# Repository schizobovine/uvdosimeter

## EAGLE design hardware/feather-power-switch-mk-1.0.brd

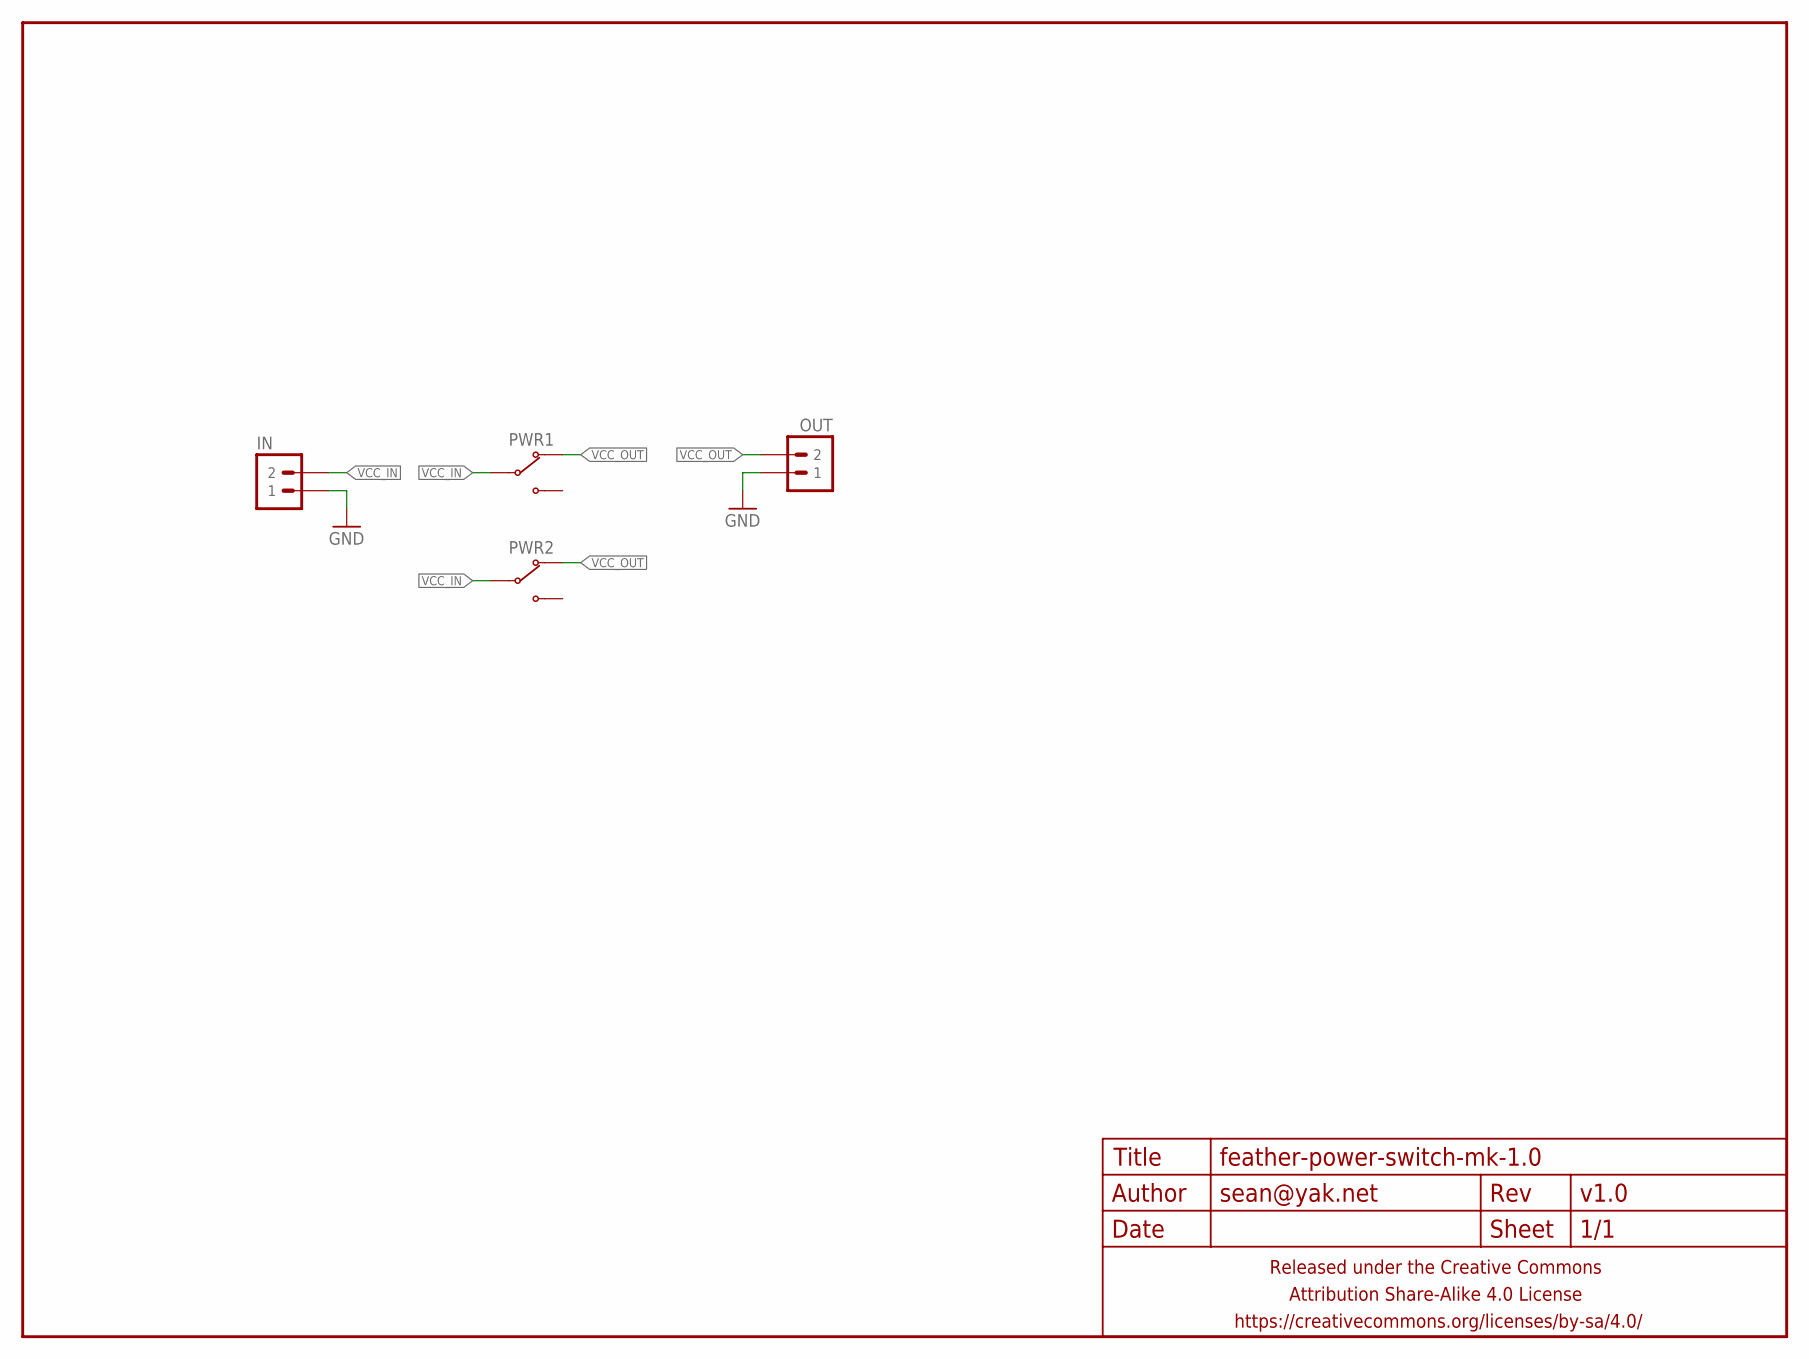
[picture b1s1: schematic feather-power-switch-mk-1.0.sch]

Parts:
FRAME1: FRAME-LETTERNO_PACKAGE; DUMMY
IN: M02JST-PTH-RA-R+; JST-2-PH-RA-PTH-R+
OUT: M02PTH-CENTERED-R+; 1X02-CENTER-R+
PWR1, PWR2: SWITCH-SPDTPCM12SMTR; SWITCH-SPDT-SMD-RA-PCM12SMTR

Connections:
GND: IN.1, OUT.1
VCC_IN: IN.2, PWR1.2 (COM), PWR2.2 (COM)
VCC_OUT: OUT.2, PWR1.1 (NC), PWR2.1 (NC)

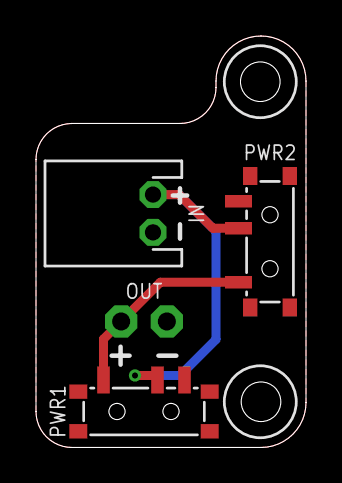
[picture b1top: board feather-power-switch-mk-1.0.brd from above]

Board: 2 copper layers, 15.0 x 22.9 mm, 5 parts (1 on the bottom side), 3 nets.

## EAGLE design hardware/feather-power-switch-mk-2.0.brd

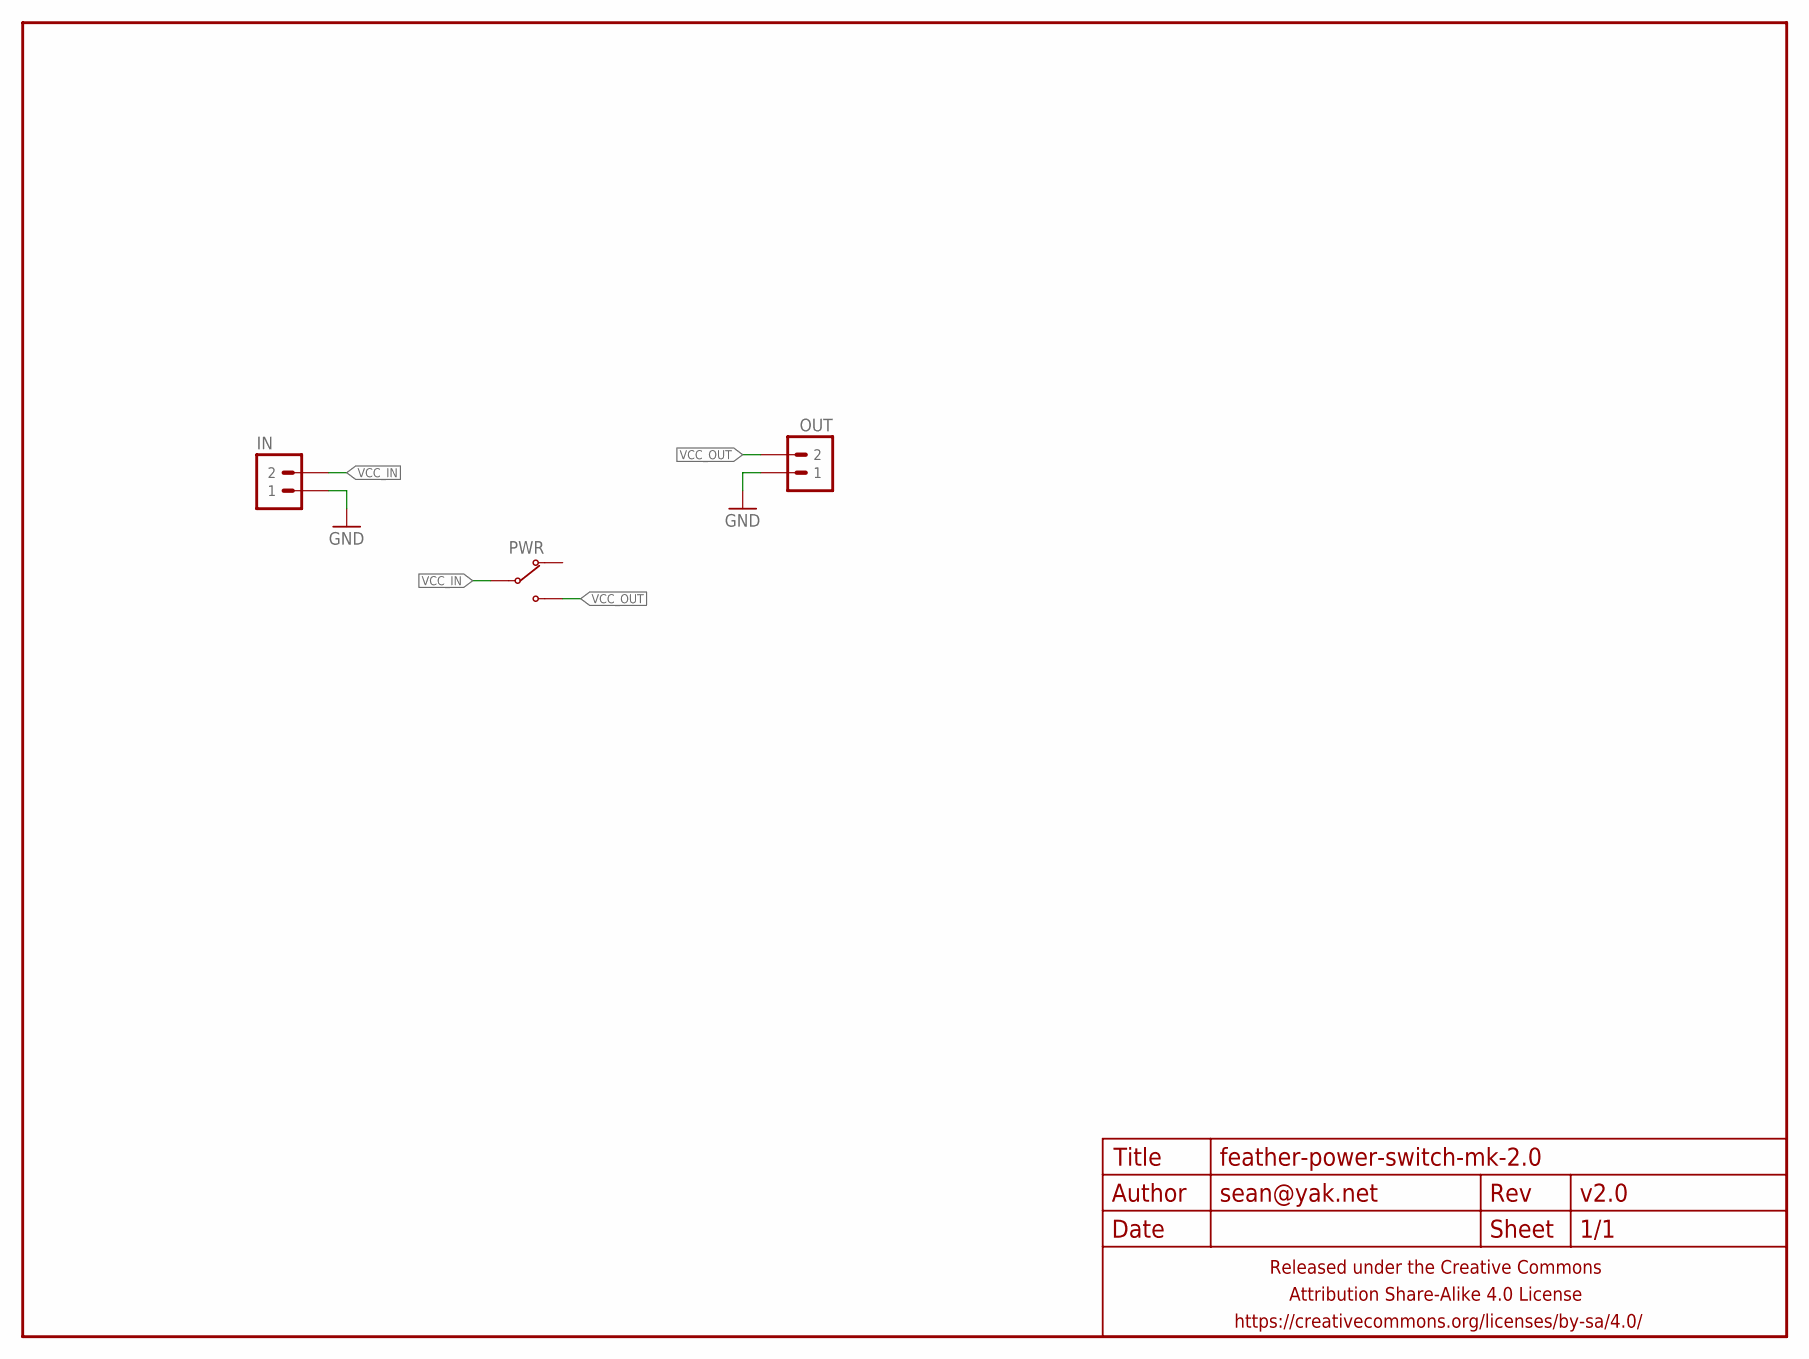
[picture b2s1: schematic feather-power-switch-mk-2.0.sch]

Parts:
FRAME1: FRAME-LETTERNO_PACKAGE; DUMMY
IN: M02PTH-CENTERED-R+; 1X02-CENTER-R+
OUT: M02PTH-CENTERED-R+; 1X02-CENTER-R+
PWR: SWITCH-SPDTSMD-RA; SWITCH-SPDT-SMD-RA

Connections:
GND: IN.1, OUT.1
VCC_IN: IN.2, PWR.2 (COM)
VCC_OUT: OUT.2, PWR.1 (NO)

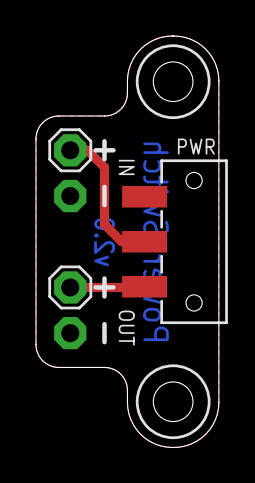
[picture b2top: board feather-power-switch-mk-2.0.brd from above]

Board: 2 copper layers, 10.2 x 22.9 mm, 4 parts (0 on the bottom side), 3 nets.

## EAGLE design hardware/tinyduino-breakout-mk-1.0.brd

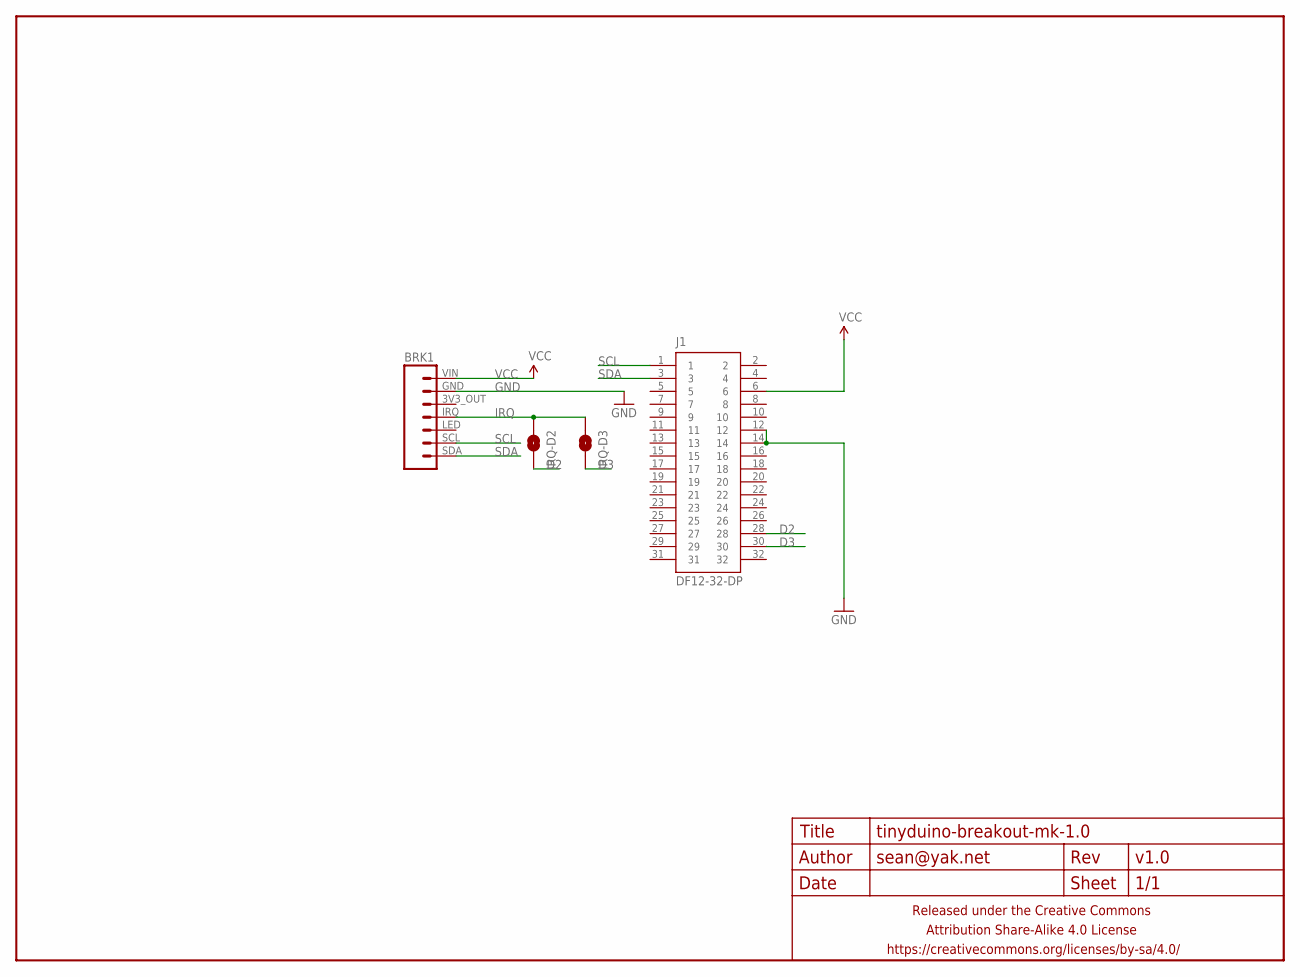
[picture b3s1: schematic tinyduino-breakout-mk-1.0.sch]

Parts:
BRK1: ADAFRUIT-SI1145-BREAKOUT
FRAME1: FRAME-LETTERNO_PACKAGE; DUMMY
IRQ-D2, IRQ-D3: JUMPER-PAD-2-NOYES_SILK; PAD-JUMPER-2-NO_YES_SILK
J1: DF12-32-DP

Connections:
D2: IRQ-D2.2, J1.28
D3: IRQ-D3.2, J1.30
GND: BRK1.GND, J1.12, J1.14
IRQ: BRK1.IRQ, IRQ-D2.1, IRQ-D3.1
SCL: BRK1.SCL, J1.1
SDA: BRK1.SDA, J1.3
VCC: BRK1.VIN, J1.6

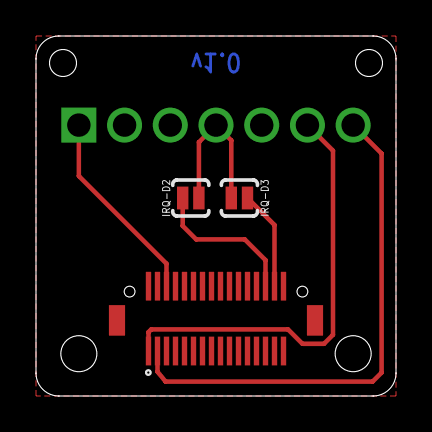
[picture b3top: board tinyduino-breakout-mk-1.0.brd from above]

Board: 2 copper layers, 20.0 x 20.0 mm, 5 parts (1 on the bottom side), 7 nets.

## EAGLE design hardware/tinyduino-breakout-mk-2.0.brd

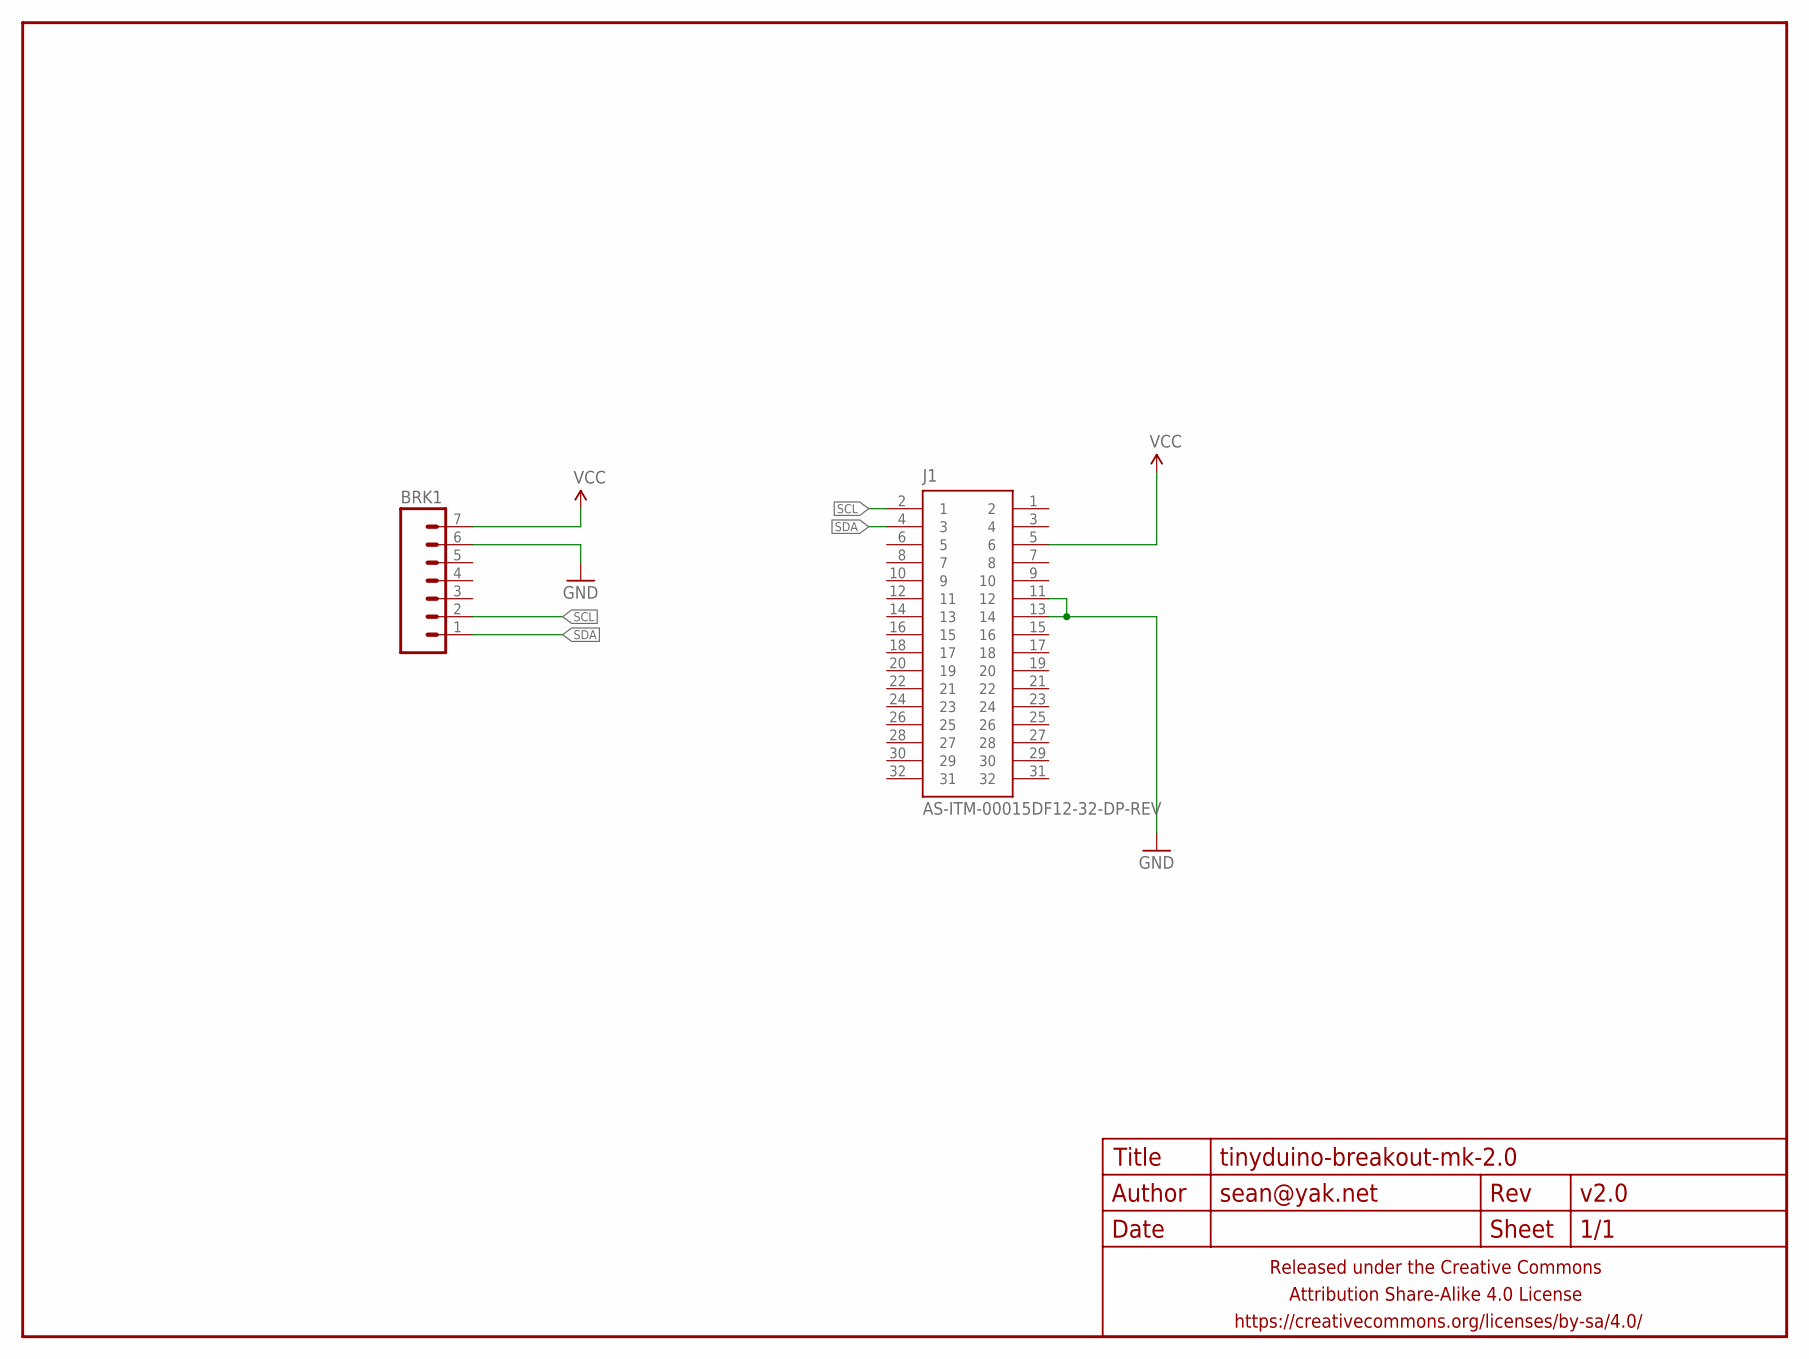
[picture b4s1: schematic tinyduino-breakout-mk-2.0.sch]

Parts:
BRK1: ADAFRUIT-SI1145-BREAKOUTSMD-RA; 1X07-SMD-SHORT
FRAME1: FRAME-LETTERNO_PACKAGE; DUMMY
J1: AS-ITM-00015DF12-32-DP-REV; DF12-32-DP

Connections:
GND: BRK1.6 (GND), J1.11 (12), J1.13 (14)
SCL: BRK1.2 (SCL), J1.2 (1)
SDA: BRK1.1 (SDA), J1.4 (3)
VCC: BRK1.7 (VIN), J1.5 (6)

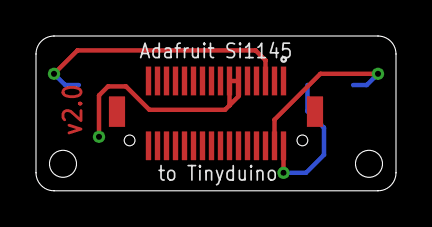
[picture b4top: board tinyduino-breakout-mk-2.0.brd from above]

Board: 2 copper layers, 20.0 x 8.6 mm, 3 parts (1 on the bottom side), 4 nets.

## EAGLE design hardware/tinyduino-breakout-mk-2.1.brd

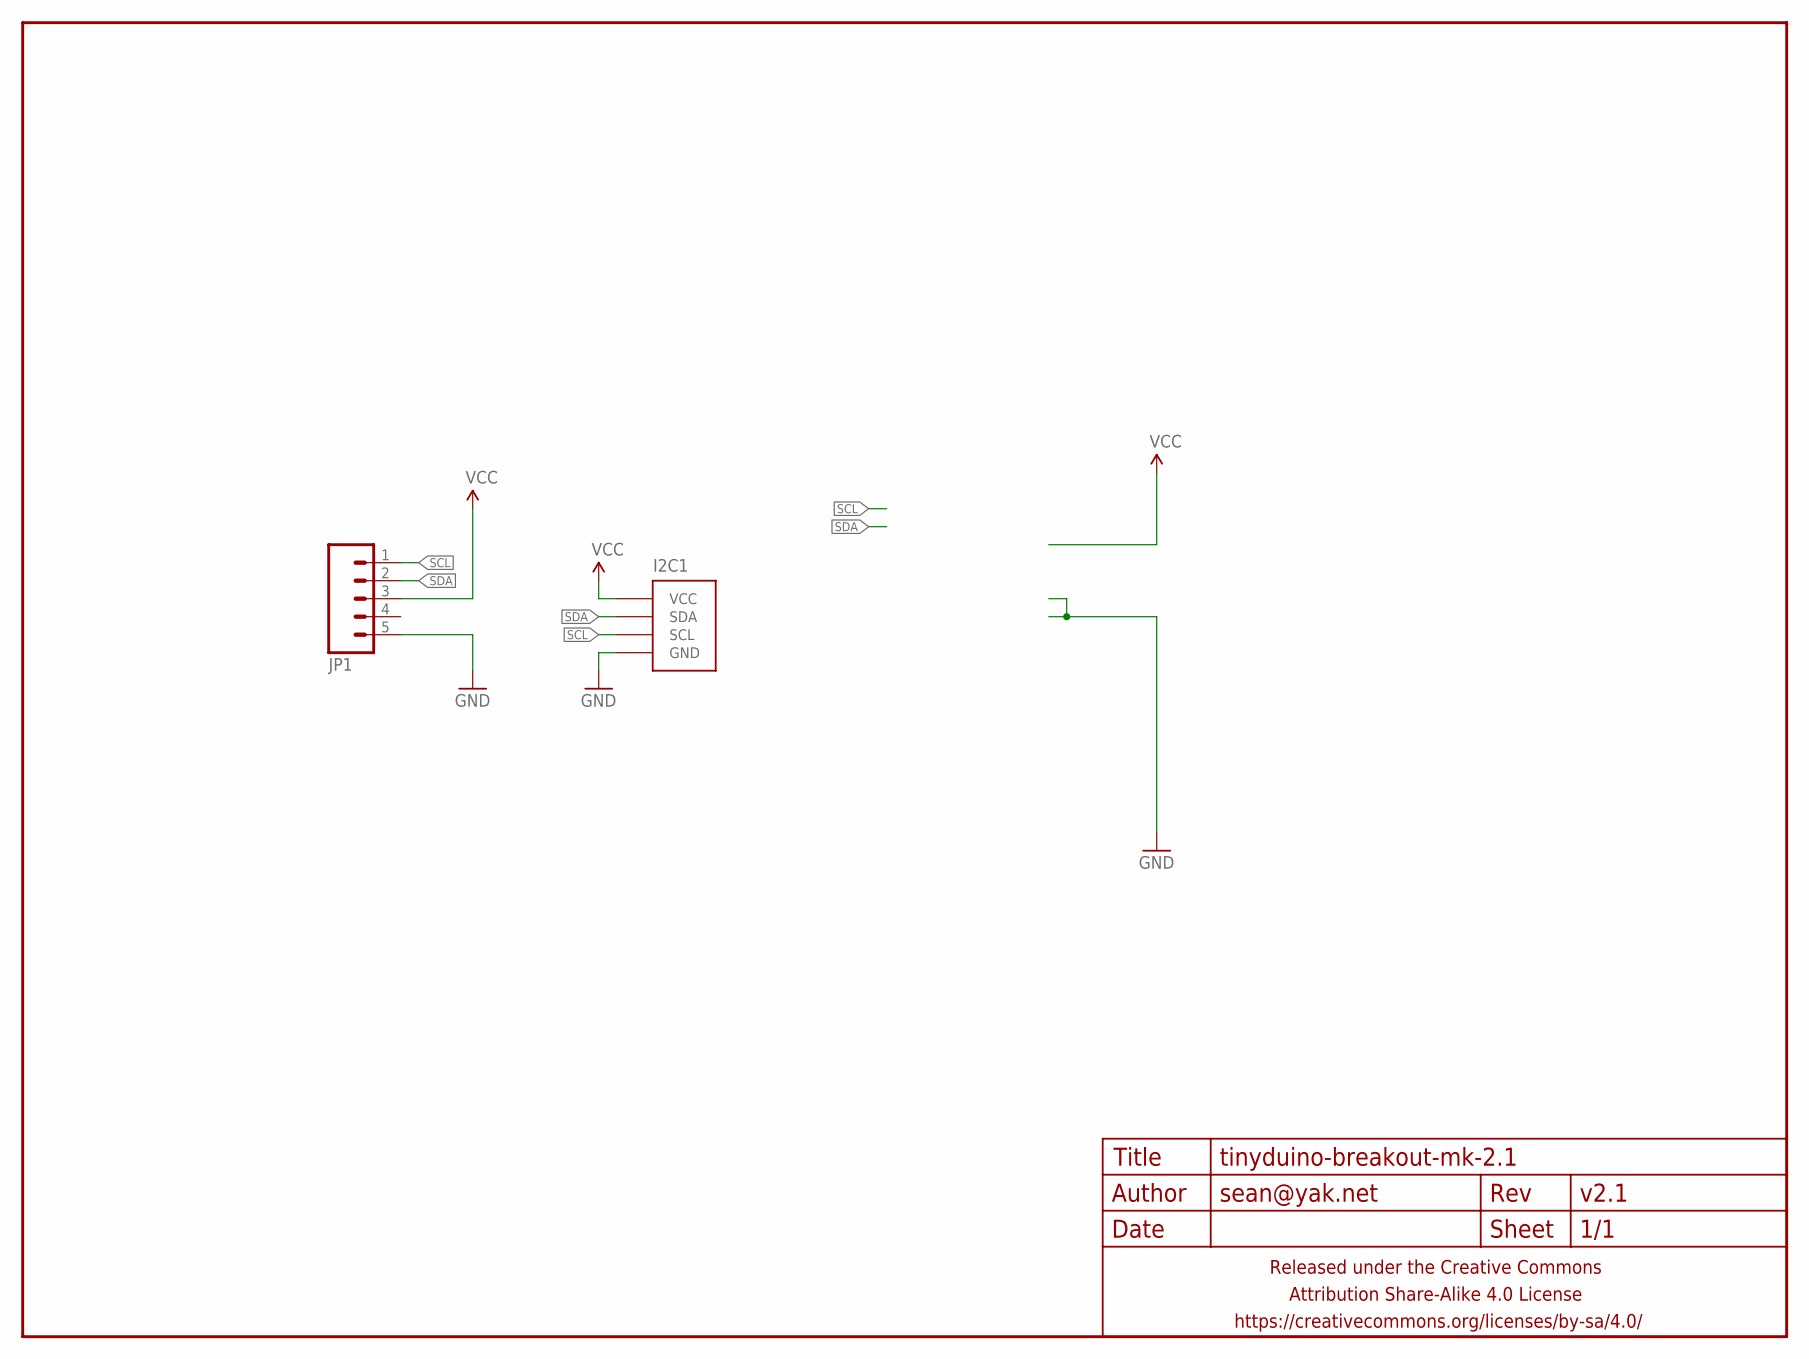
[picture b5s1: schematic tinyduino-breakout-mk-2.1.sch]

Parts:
FRAME1: FRAME-LETTERNO_PACKAGE; DUMMY
I2C1: M04-I2CTINDUINO-CONNECTOR-REV; DF12-32-DP-I2CONLY
JP1: M05SMD-SHORT; 1X05-SMD-SHORT

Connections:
GND: I2C1.11 (GND), I2C1.13 (GND), JP1.5
SCL: JP1.1
SDA: JP1.2
VCC: I2C1.5 (VCC), JP1.3

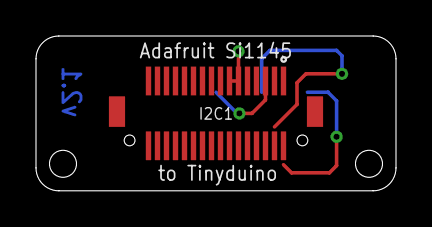
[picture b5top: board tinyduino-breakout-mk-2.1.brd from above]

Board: 2 copper layers, 20.0 x 8.6 mm, 3 parts (1 on the bottom side), 2 nets.

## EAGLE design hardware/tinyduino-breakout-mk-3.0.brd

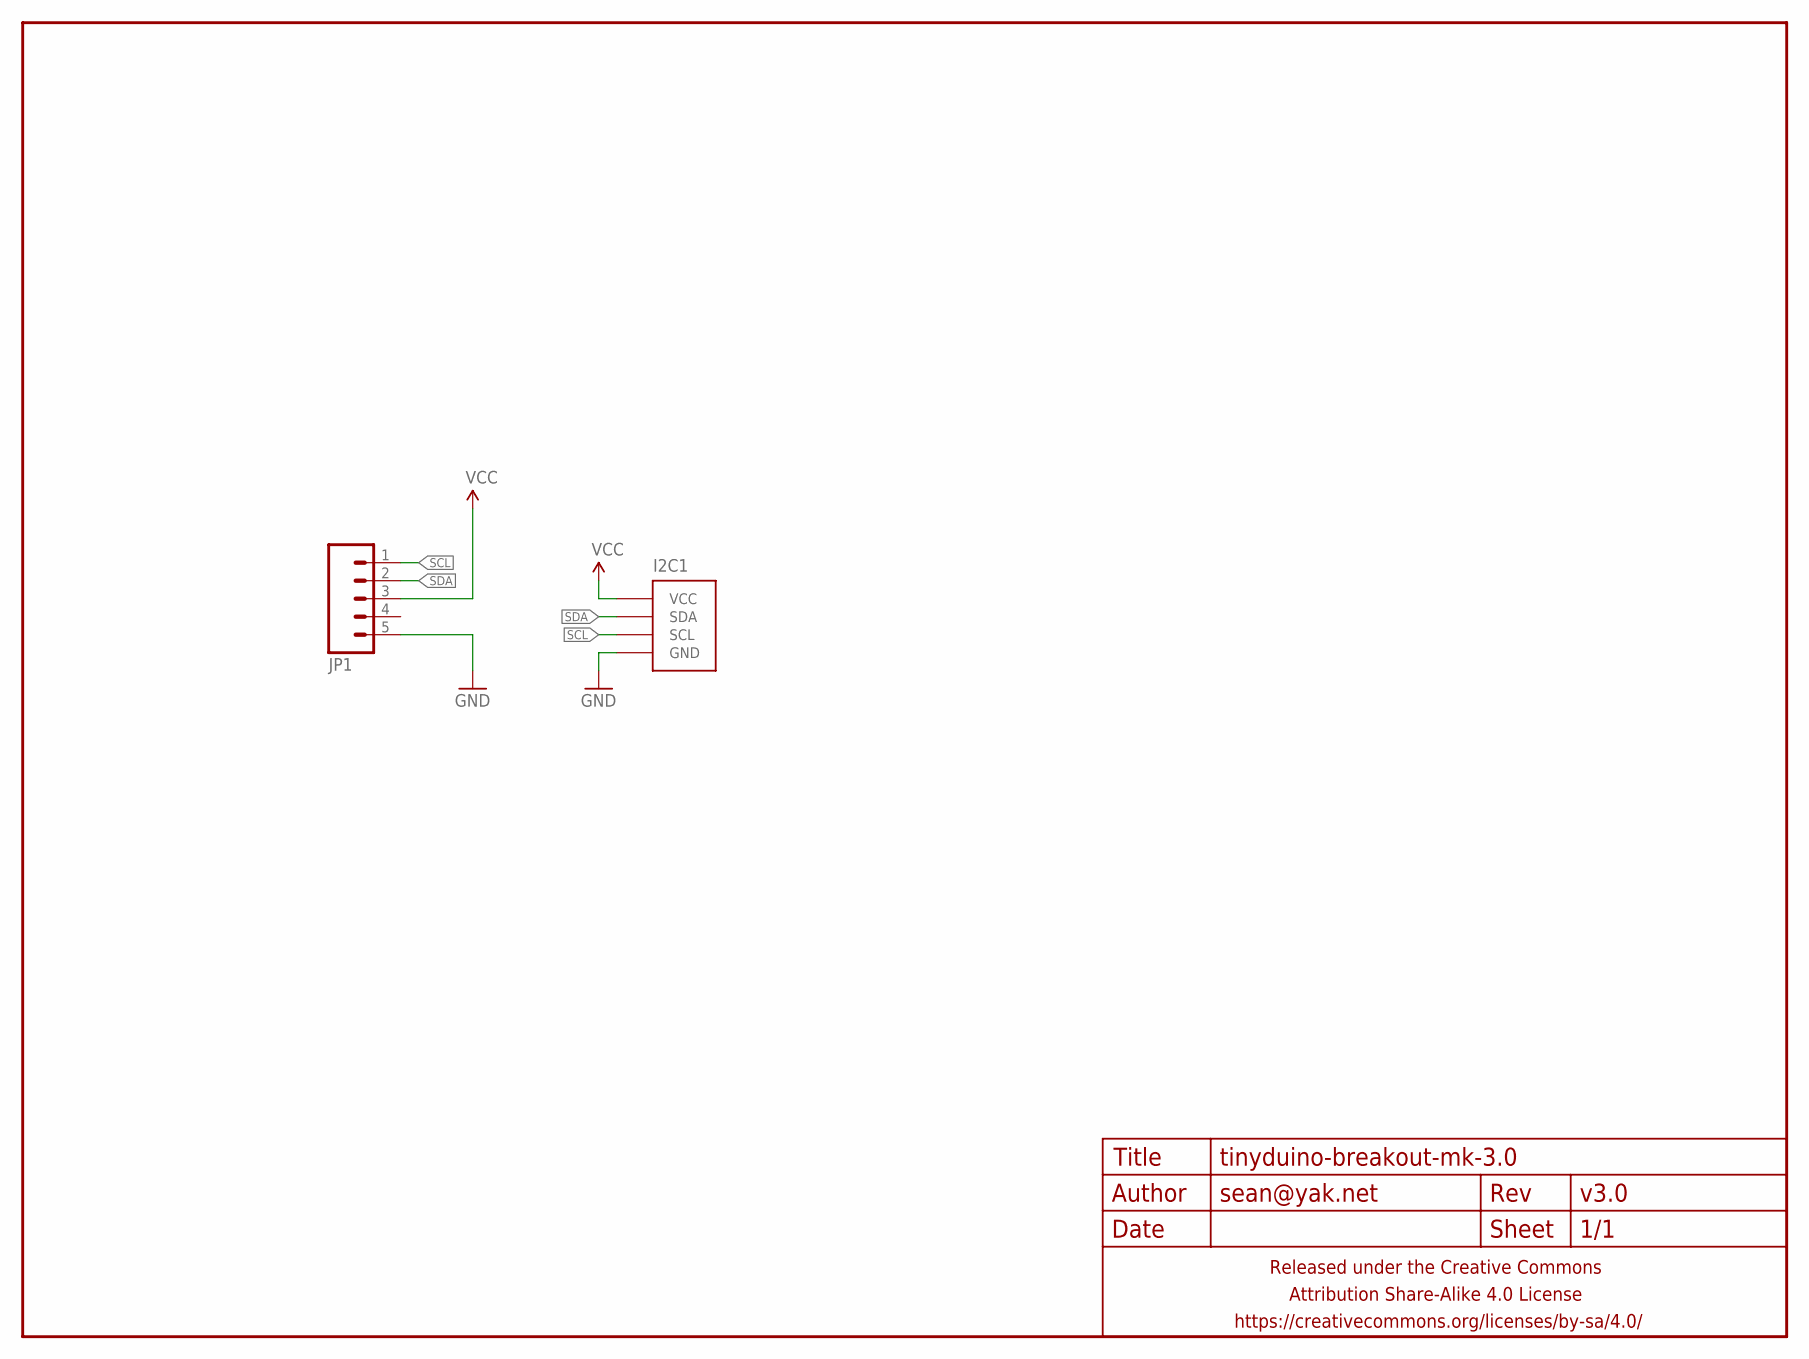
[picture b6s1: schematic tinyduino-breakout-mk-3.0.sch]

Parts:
FRAME1: FRAME-LETTERNO_PACKAGE; DUMMY
I2C1: M04-I2CTINYDUINO-CONNECTOR-REV; DF12-32-DP-I2CONLY-REV
JP1: M05SMD-SHORT; 1X05-SMD-SHORT

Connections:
GND: I2C1.12 (GND), I2C1.14 (GND), JP1.5
SCL: I2C1.1 (SCL), JP1.1
SDA: I2C1.3 (SDA), JP1.2
VCC: I2C1.2 (VCC), JP1.3

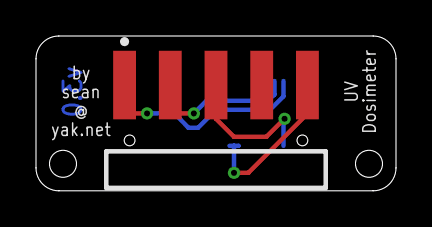
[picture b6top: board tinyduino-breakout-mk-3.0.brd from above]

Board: 2 copper layers, 20.0 x 8.6 mm, 3 parts (0 on the bottom side), 4 nets.

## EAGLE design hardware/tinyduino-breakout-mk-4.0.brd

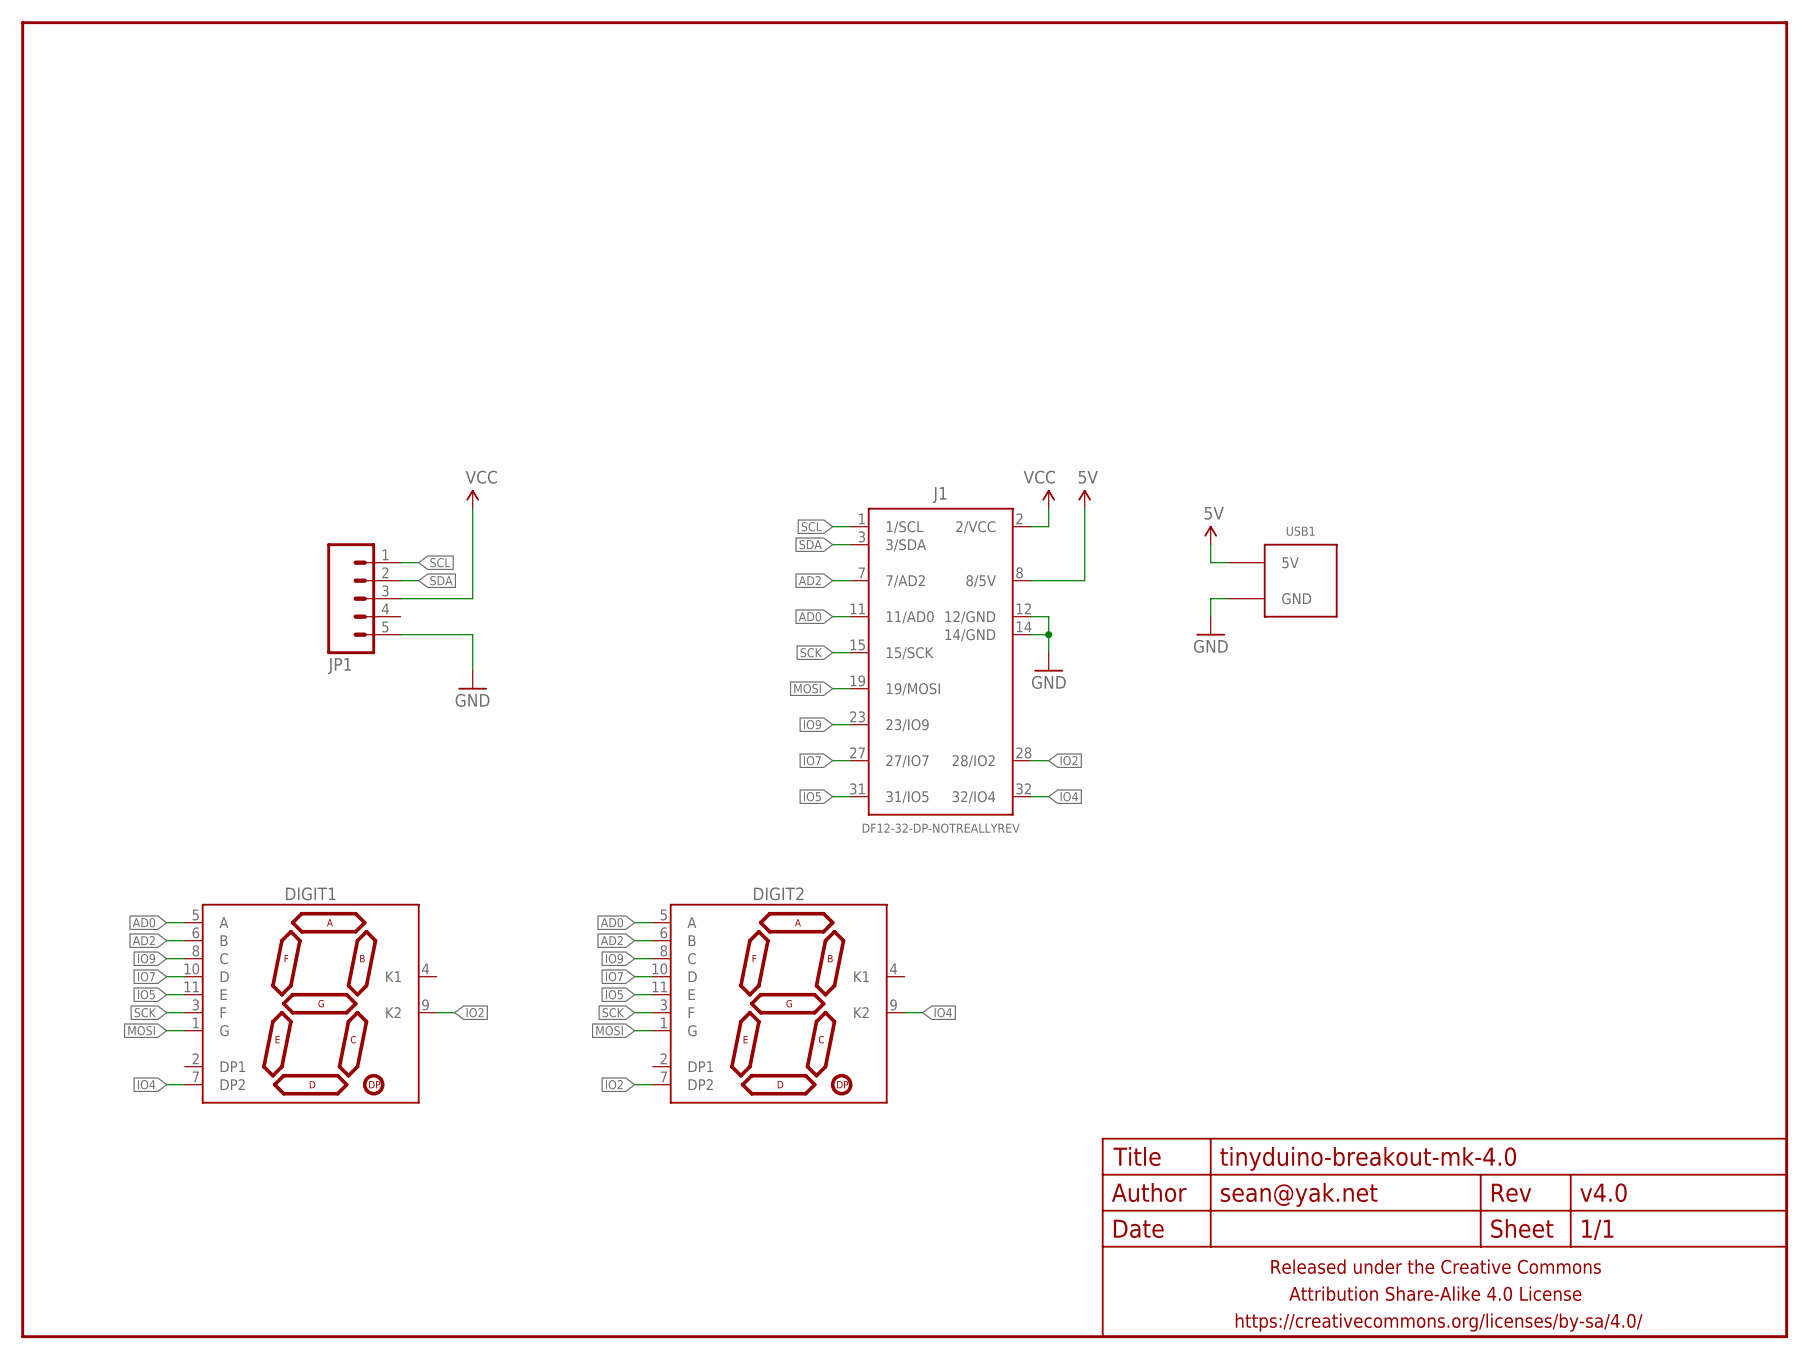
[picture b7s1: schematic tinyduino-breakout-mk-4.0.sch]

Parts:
DIGIT1, DIGIT2: 7SEG_1DIG_2DP7MM_CC_SMT; 7SEG_1DIG_7MM_SMT
FRAME1: FRAME-LETTERNO_PACKAGE; DUMMY
J1: DF12-32-DP-NOTREALLYREV; DF12-32-DP-I2C+EXTRA-REV
JP1: M05PTH-CENTERED; 1X05_PTH_CENTERED
USB1: USB_AB_PWRONLY; FCI-10103594-USB-MICRO-B-PWRONLY

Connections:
5V: J1.8 (8/5V), USB1.1 (5V)
AD0: DIGIT1.5 (A), DIGIT2.5 (A), J1.11 (11/AD0)
AD2: DIGIT1.6 (B), DIGIT2.6 (B), J1.7 (7/AD2)
GND: J1.12 (12/GND), J1.14 (14/GND), JP1.5, USB1.5 (GND), USB1.SHIELD@1 (GND), USB1.SHIELD@2 (GND), USB1.SHIELD@3 (GND), USB1.SHIELD@4 (GND)
IO2: DIGIT1.9 (K2), DIGIT2.7 (DP2), J1.28 (28/IO2)
IO4: DIGIT1.7 (DP2), DIGIT2.9 (K2), J1.32 (32/IO4)
IO5: DIGIT1.11 (E), DIGIT2.11 (E), J1.31 (31/IO5)
IO7: DIGIT1.10 (D), DIGIT2.10 (D), J1.27 (27/IO7)
IO9: DIGIT1.8 (C), DIGIT2.8 (C), J1.23 (23/IO9)
MOSI: DIGIT1.1 (G), DIGIT2.1 (G), J1.19 (19/MOSI)
SCK: DIGIT1.3 (F), DIGIT2.3 (F), J1.15 (15/SCK)
SCL: J1.1 (1/SCL), JP1.1
SDA: J1.3 (3/SDA), JP1.2
VCC: J1.2 (2/VCC), JP1.3

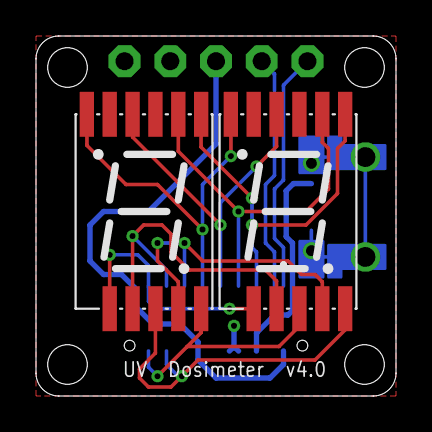
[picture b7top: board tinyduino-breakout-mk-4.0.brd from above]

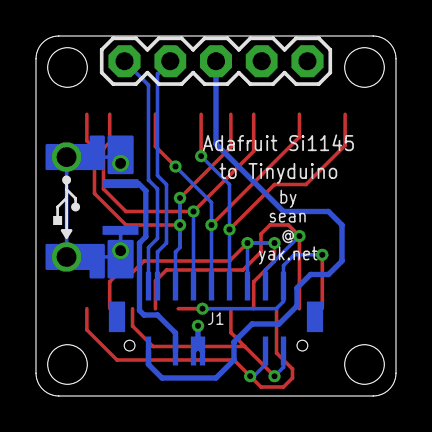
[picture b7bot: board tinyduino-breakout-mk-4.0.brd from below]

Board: 2 copper layers, 20.0 x 20.0 mm, 6 parts (2 on the bottom side), 14 nets.

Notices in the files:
parts and their libraries:
A_butts: Released under the Creative Commons Attribution Share-Alike 4.0 License
A_butts: https://creativecommons.org/licenses/by-sa/4.0
A_butts: Released under the Creative Commons
